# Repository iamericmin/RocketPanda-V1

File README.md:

# Rocket Panda Mk. I
# [Full write-up is on my website!](https://iamericmin.github.io/rocketpanda1.html)

## nRF52832 dev kit designed for experiments with BLE

Project status: very early in development. THIS IS A PROTOTYPE AND IS CURRENTLY VERY MESSY!

# What is this?
The Rocket Panda is an nRF52832 dev kit that I will use to prototype my future projects. I already have the nRF52832-DK, but I believe the best way to learn a chip is to make a breakout board for it. This is also my first ever project with a built in USB-serial converter. The Rocket Panda gets the funky name from its black and white PCB.

# SPEC SHEET:
- PROCESSOR: nRF52832 Soc. 64MHz ARM cortex M4 with 64k RAM and 512k flash
- BOOTLOADER: Adafruit custom nRF52 DFU bootloader
- CONNECTORS: Triple 2x10 2.54mm pin headers, Cortex debug header, JST-PH Serial connector, USB serial connector
- I/O: Reset button, user button, power LED, RX/TX LEDs, and two auxilliary LEDs.
- POWER: CR2032 coin cell or USB mini-B jack
- DIMENSIONS: Credit card size(85.6mm x 54mm)

# Repo structure
The rocketpanda_fw folder contains everything related to the Rocket Panda's firmware. This includes a Platform IO project folder, Adafruit's custom DFU bootloader, and Nordic's J-Link recovery firmware for the nRF52DK.
The rocketpanda_hw folder contains everything hardware related, such as eagle files, schematics, and BOM. It also includes the hardware files for Adafruit's nRF52832 feather board since I used it as a close reference when designing the Rocket Panda.

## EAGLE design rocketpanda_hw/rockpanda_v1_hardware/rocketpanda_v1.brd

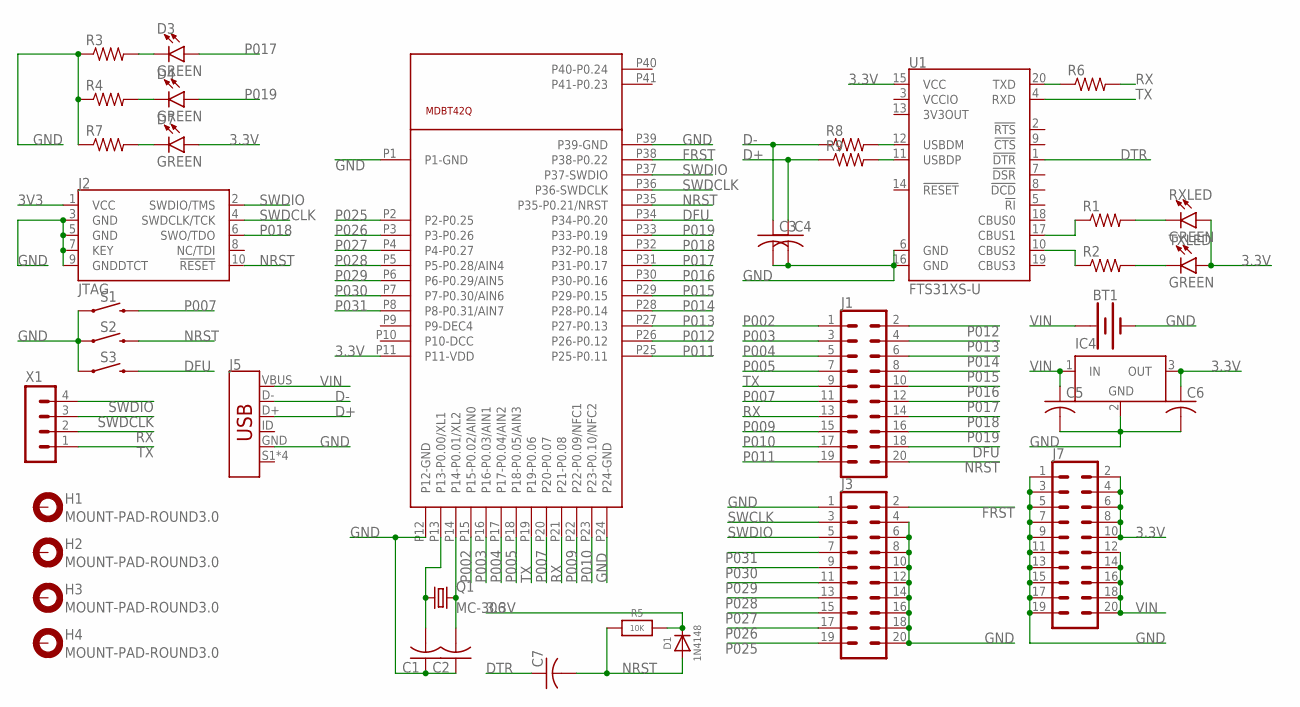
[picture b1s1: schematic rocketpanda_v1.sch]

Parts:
BT1: BATTERY-20MM_SMD_4LEGS_OVERPASTE_INNER; BATTCON_20MM_4LEGS_OVERPASTE_INNER
C1, C2, C3, C4, C5, C6, C7: C-USC0805; C0805
D1: 1N4148; SOD-323
D3, D4, D7: GREEN; LED-1206@1
H1, H2, H3, H4: MOUNT-PAD-ROUND3.0; 3,0-PAD
IC4: LT1129CST5; SOT223
J1, J3, J7: CONN_10X22X10_LOCK; 2X10_LOCK
J2: JTAG; 2X5-SMD-1.27MM
J5: USB_MINI-B_SMT; USB-MINIB
Q1: MC-306
R1, R2, R3, R4, R6, R7, R8, R9: R-US_M0805; M0805
R5: 10K; 0805-NO
RXLED: GREEN; LED-1206@1
S1, S2: MOMENTARY-SWITCH-SPST-SMD-5.2MM; TACTILE_SWITCH_SMD_5.2MM
S3: MOMENTARY-SWITCH-SPST-SMD-4.6X2.8MM; TACTILE_SWITCH_SMD_4.6X2.8MM
TXLED: GREEN; LED-1206@1
U1: FTS31XS-U; SSOP20_L
U$1: MDBT42Q; MDBT40
X1: B4B-PH-SM4-TB

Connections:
3.3V: C6.1, D1.C, D7.A, IC4.3 (OUT), J7.2, J7.4, J7.6, J7.8, J7.10, R5.2, RXLED.A, TXLED.A, U1.15 (VCC), U$1.P11 (P11-VDD)
3V3: J2.1 (VCC)
D+: C4.1, J5.D+, R9.1
D-: C3.1, J5.D-, R8.1
DFU: J1.18, S3.3 (2), S3.4 (2), U$1.P34 (P34-P0.20)
DTR: C7.1, U1.1 (!DTR)
FRST: J3.2, U$1.P38 (P38-P0.22)
GND: BT1.2 (-), C1.1, C2.1, C3.2, C4.2, C5.2, C6.2, IC4.2 (GND), IC4.4 (GND), J2.3 (GND), J2.5 (GND), J2.7 (KEY), J2.9 (GNDDTCT), J3.1, J3.4, J3.6, J3.8, J3.10, J3.12, J3.14, J3.16, J3.18, J3.20, J5.GND, J7.1, J7.3, J7.5, J7.7, J7.9, J7.11, J7.13, J7.15, J7.17, J7.19, R3.1, R4.1, R7.1, S1.1, S2.1, S3.1, S3.2 (1), U1.6 (GND), U1.16 (GND), U$1.P1 (P1-GND), U$1.P12 (P12-GND), U$1.P24 (P24-GND), U$1.P39 (P39-GND)
unnamed: D3.C, R3.2
unnamed: D4.C, R4.2
unnamed: C2.2, Q1.4 (2), U$1.P14 (P14-P0.01/XL2)
unnamed: C1.2, Q1.1, U$1.P13 (P13-P0.00/XL1)
unnamed: D7.C, R7.2
unnamed: R6.1, U1.20 (TXD)
unnamed: R1.2, RXLED.C
unnamed: R2.2, TXLED.C
unnamed: R1.1, U1.17 (CBUS1)
unnamed: R2.1, U1.10 (CBUS2)
unnamed: R8.2, U1.12 (USBDM)
unnamed: R9.2, U1.11 (USBDP)
NRST: C7.2, D1.A, J1.20, J2.10 (!RESET), R5.1, S2.3 (2), U$1.P35 (P35-P0.21/NRST)
P002: J1.1, U$1.P15 (P15-P0.02/AIN0)
P003: J1.3, U$1.P16 (P16-P0.03/AIN1)
P004: J1.5, U$1.P17 (P17-P0.04/AIN2)
P005: J1.7, U$1.P18 (P18-P0.05/AIN3)
P007: J1.11, S1.3 (2), U$1.P20 (P20-P0.07)
P009: J1.15, U$1.P22 (P22-P0.09/NFC1)
P010: J1.17, U$1.P23 (P23-P0.10/NFC2)
P011: J1.19, U$1.P25 (P25-P0.11)
P012: J1.2, U$1.P26 (P26-P0.12)
P013: J1.4, U$1.P27 (P27-P0.13)
P014: J1.6, U$1.P28 (P28-P0.14)
P015: J1.8, U$1.P29 (P29-P0.15)
P016: J1.10, U$1.P30 (P30-P0.16)
P017: D3.A, J1.12, U$1.P31 (P31-P0.17)
P018: J1.14, J2.6 (SWO/TDO), U$1.P32 (P32-P0.18)
P019: D4.A, J1.16, U$1.P33 (P33-P0.19)
P025: J3.19, U$1.P2 (P2-P0.25)
P026: J3.17, U$1.P3 (P3-P0.26)
P027: J3.15, U$1.P4 (P4-P0.27)
P028: J3.13, U$1.P5 (P5-P0.28/AIN4)
P029: J3.11, U$1.P6 (P6-P0.29/AIN5)
P030: J3.9, U$1.P7 (P7-P0.30/AIN6)
P031: J3.7, U$1.P8 (P8-P0.31/AIN7)
RX: J1.13, R6.2, U$1.P21 (P21-P0.08), X1.2
SWCLK: J3.3
SWDCLK: J2.4 (SWDCLK/TCK), U$1.P36 (P36-SWDCLK), X1.3
SWDIO: J2.2 (SWDIO/TMS), J3.5, U$1.P37 (P37-SWDIO), X1.4
TX: J1.9, U1.4 (RXD), U$1.P19 (P19-P0.06), X1.1
VIN: BT1.1 (+), C5.1, IC4.1 (IN), J5.VBUS, J7.12, J7.14, J7.16, J7.18, J7.20

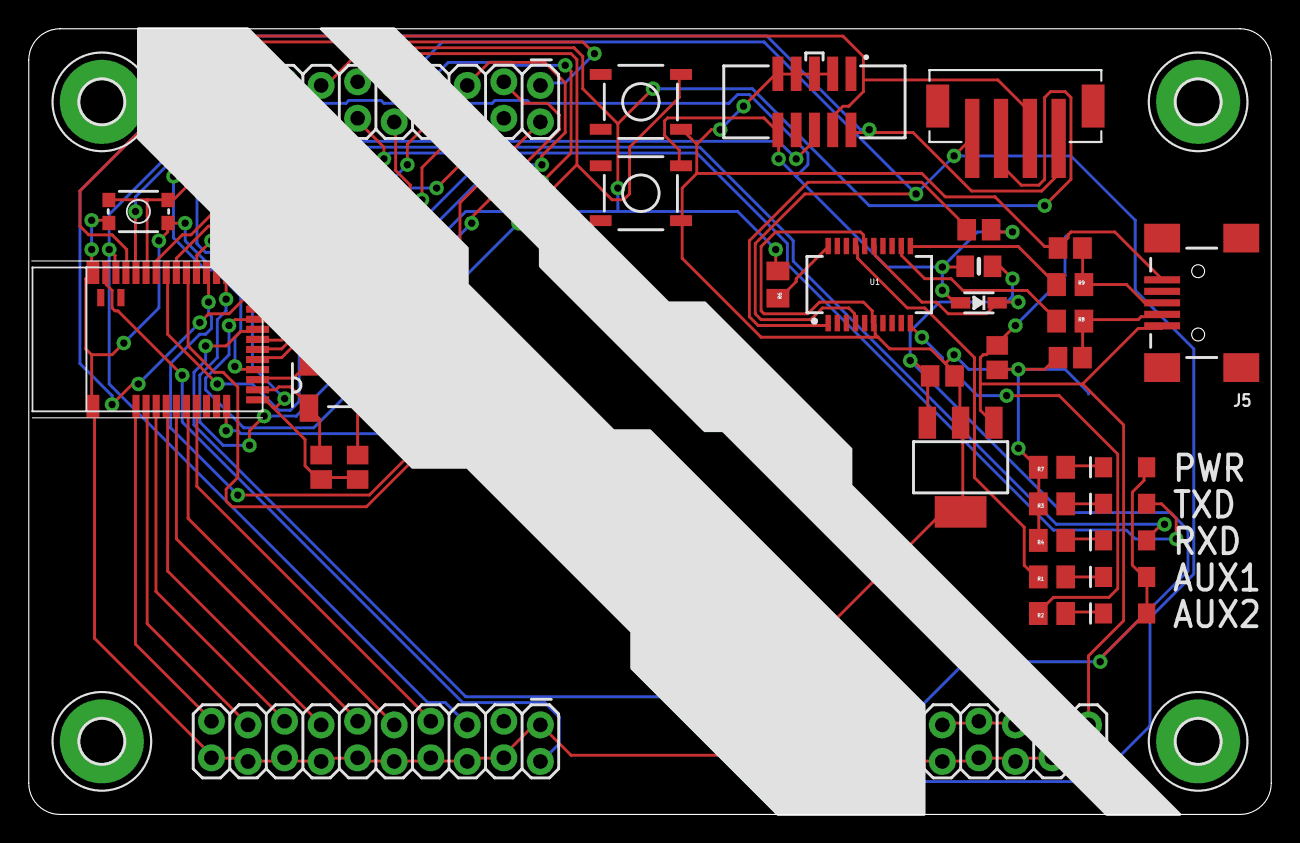
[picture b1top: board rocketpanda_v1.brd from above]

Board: 2 copper layers, 86.4 x 54.6 mm, 40 parts (1 on the bottom side), 48 nets.

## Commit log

2020-02-03 first
2020-02-03 added repo structure
2020-02-03 updated repo structure
    updated repo structure
2020-02-06 updated hardware files!

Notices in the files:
parts and their libraries:
SparkFun-Connectors: Licensing: Creative Commons ShareAlike 4.0 International - https://creativecommons.org/licenses/by-sa/4.0
SparkFun-DigitalIC: Licensing: CC v3.0 Share-Alike You are welcome to use this library for commercial purposes.
